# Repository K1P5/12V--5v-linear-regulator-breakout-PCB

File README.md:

# 12V--5v-linear-regulator-breakout-PCB
12VDC to 5VDC linear regulator breakout PCB for prototyping

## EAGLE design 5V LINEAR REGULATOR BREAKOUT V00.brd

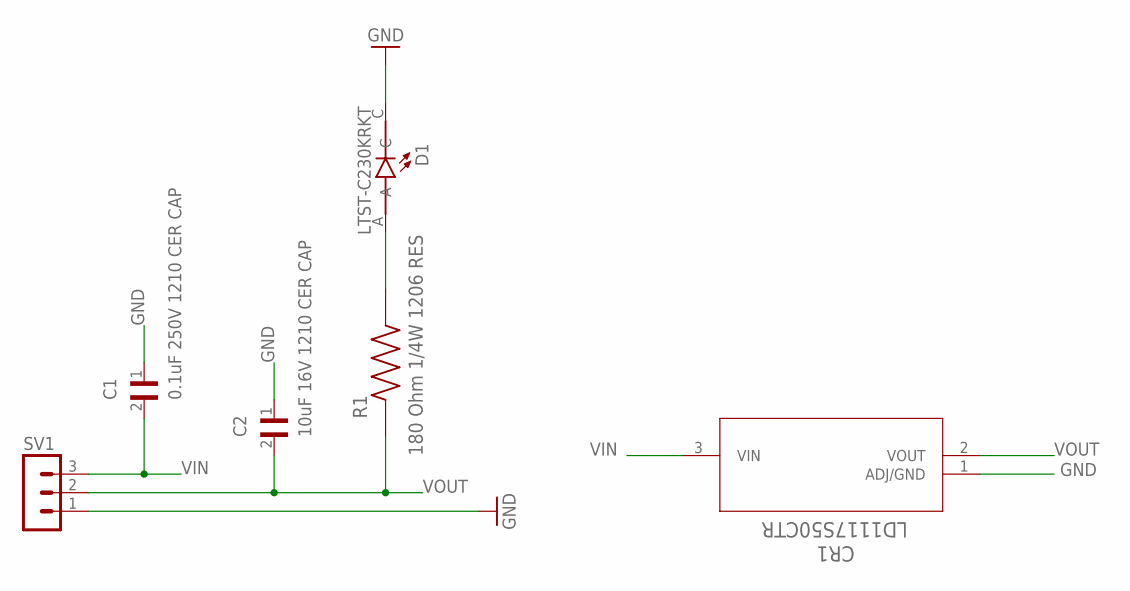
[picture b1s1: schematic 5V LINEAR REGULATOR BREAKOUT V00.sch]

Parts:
C1: 0.1uF 250V 1210 CER CAP; CAPC3225X280
C2: 10uF 16V 1210 CER CAP; CAPC3225X280
CR1: LD1117S50CTR; SOT-223_STM
D1: LTST-C230KRKT; LEDC3216X110
R1: 180 Ohm 1/4W 1206 RES; RESC3116X65N
SV1: MA03-1

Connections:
GND: C1.1, C2.1, CR1.1 (ADJ/GND), D1.C, SV1.1
unnamed: D1.A, R1.2
VIN: C1.2, CR1.3 (VIN), SV1.3
VOUT: C2.2, CR1.2 (VOUT), R1.1, SV1.2

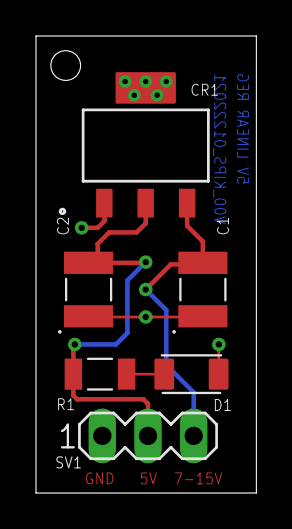
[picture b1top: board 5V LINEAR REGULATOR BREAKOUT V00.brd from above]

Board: 2 copper layers, 12.2 x 25.4 mm, 6 parts (0 on the bottom side), 4 nets.

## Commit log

2021-01-30 Create ignore
2021-01-30 Eagle file commits
